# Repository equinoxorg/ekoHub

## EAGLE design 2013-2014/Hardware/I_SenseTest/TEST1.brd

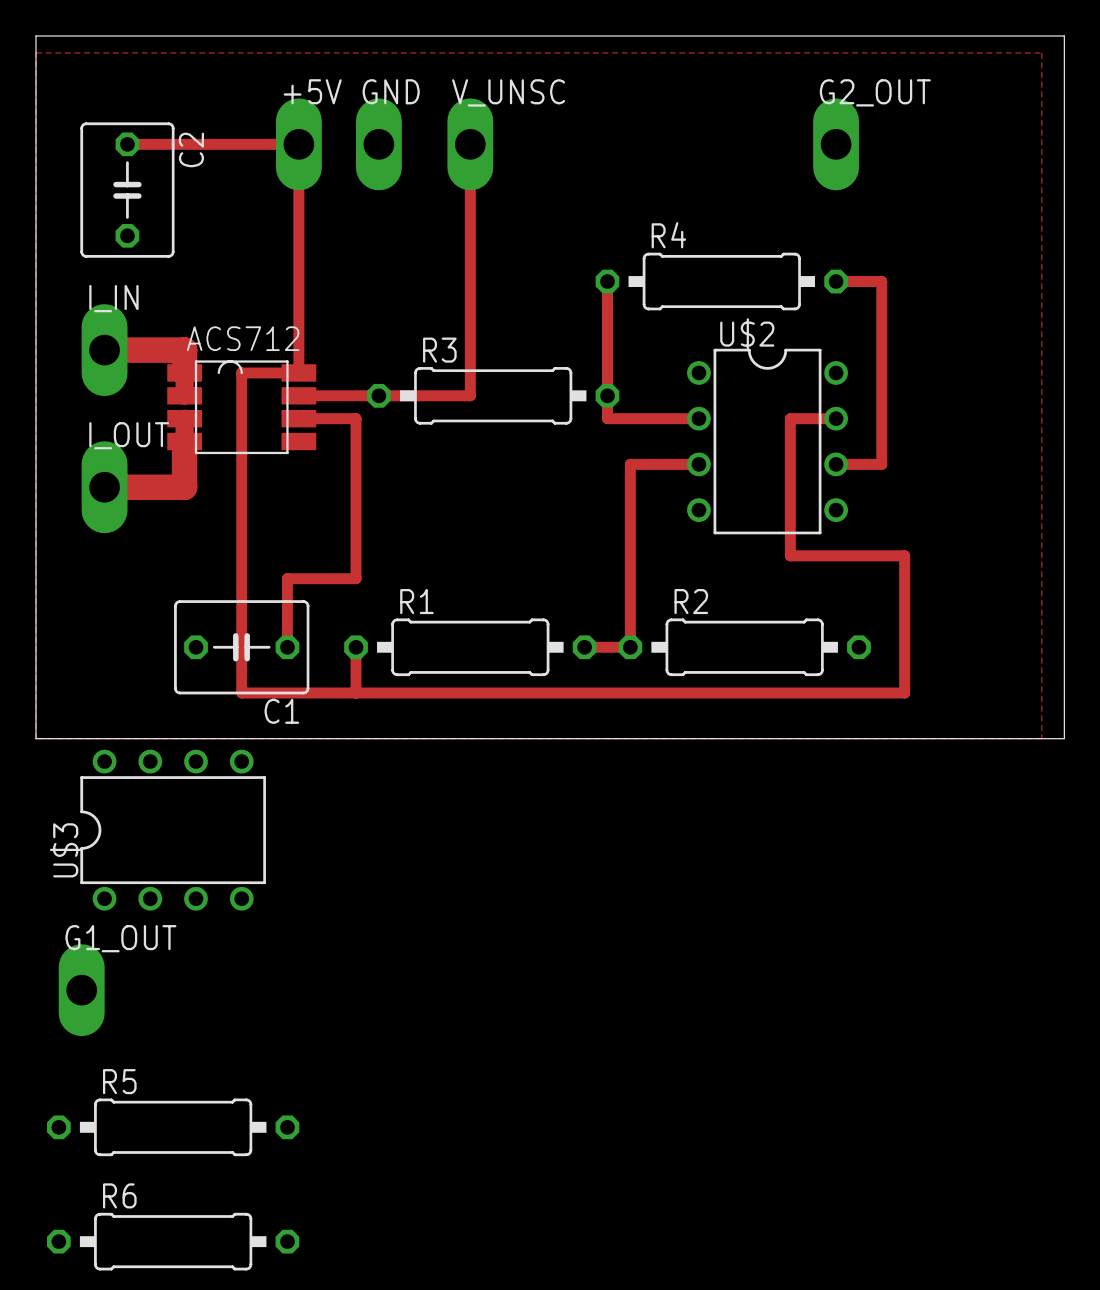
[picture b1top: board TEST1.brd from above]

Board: 2 copper layers, 57.1 x 39.0 mm, 18 parts (0 on the bottom side), 11 nets.

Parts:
+5V: TPPAD1-17Y; P1-17Y
C1: 1n; C050-050X075
C2: 100n; C050-050X075
G1_OUT, G2_OUT: TPPAD1-17Y; P1-17Y
GND: TPPAD1-17Y; P1-17Y
I_IN: TPPAD1-17Y; P1-17Y
I_OUT: TPPAD1-17Y; P1-17Y
R1, R2, R3, R6: 1k; 0309/12
R4: 1.5k; 0309/12
R5: 2k; 0309/12
U$1: ACS712; SOIC8
U$2, U$3: MCP601; PDIP8
V_UNSC: TPPAD1-17Y; P1-17Y

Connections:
+2.5V: R1.2, R2.1, U$2.3, U$3.3
+5V: +5V.TP, C2.1, R1.1, U$1.8, U$2.7, U$3.7
G1_OUT: G1_OUT.TP, R4.2, R5.1, U$2.6
G2_OUT: G2_OUT.TP, R6.2, U$3.6
GND: C1.2, C2.2, GND.TP, R2.2, U$1.5, U$2.4, U$3.4
I_IN: I_IN.TP, U$1.1, U$1.2
I_OUT: I_OUT.TP, U$1.3, U$1.4
unnamed: R3.1, U$1.7, V_UNSC.TP
unnamed: R3.2, R4.1, U$2.2
unnamed: R5.2, R6.1, U$3.2
unnamed: C1.1, U$1.6

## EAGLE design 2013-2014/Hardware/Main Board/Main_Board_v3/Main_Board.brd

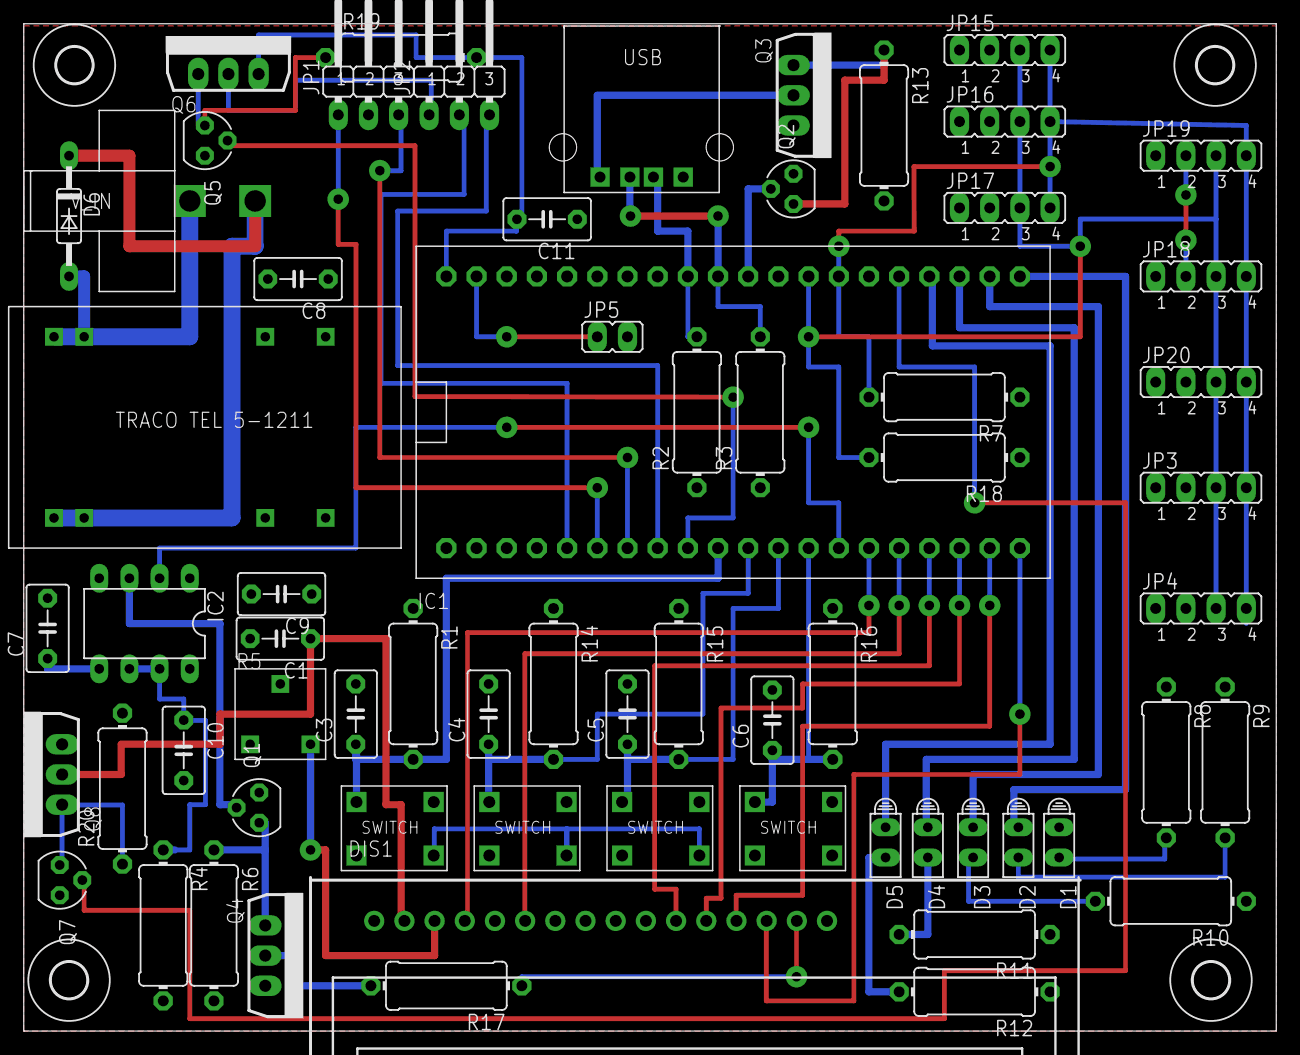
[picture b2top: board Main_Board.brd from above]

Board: 2 copper layers, 105.4 x 84.8 mm, 69 parts (0 on the bottom side), 50 nets.

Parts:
C1, C3, C4, C5, C6, C8, C11: 100nF; C5B3.5
C7: 10nF/0.01u; C5B3.5
C9: 10uF; C5B3.5
C10: 10n; C5B3.5
D1, D2, D3, D4, D5: HLMP6
D6: 1N4148DO35-10; DO35-10
DIS1: TUXGR_16X2_R2
IC1: MBED_MICROCONTROLLER; DIL40_0.9
IC2: NE555; DIL-08
JP1, JP2: JP2W
JP3, JP4, JP15, JP16, JP17, JP18, JP19, JP20: JP4
JP5: JP1
Q1, Q2, Q5, Q7: BS170; SOT54E
Q3, Q4, Q6, Q8: IRF3704L-V; TO262-V
R1, R14, R15, R16: 1K; 0411/12
R2, R3, R7, R8, R9, R10, R11, R12, R18: 0411/12
R4: 300k; 0411/12
R5: IRG2014TRIM
R6, R13, R19, R20: 1M; 0411/12
R17: 20; 0411/12
U$1: USBA_SOCKET
U$4: INPUT_VOLTAGE_CONNECTOR
U$5, U$6, U$7, U$8: TACT_SWITCH
U$9: TRACO_ISOLATED_SUPPLY
U$10, U$11, U$12, U$13: 3,0

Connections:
3V3: JP2.1, Q6.2
3V3_MBED: C11.2, IC1.40, Q6.3, R19.2
5V_MBED: IC1.39, JP5.1
D+: IC1.31, R3.2, U$1.D++
D-: IC1.32, R2.2, U$1.D--
GND: C1.2, C3.2, C4.2, C5.2, C6.2, C7.2, C8.2, C9.2, C10.2, C11.1, DIS1.1, DIS1.5, DIS1.16, IC1.1, IC2.1, JP1.2, JP3.2, JP4.2, JP15.2, JP16.2, JP17.2, JP18.2, JP19.2, JP20.2, Q1.S, Q2.S, Q5.S, Q7.S, R1.1, R2.1, R3.1, R5.P$1, R5.P$2, R8.1, R9.1, R10.1, R11.1, R12.1, R14.1, R15.1, R16.1, U$1.GND, U$9.P$16
MODEM: Q3.2, U$1.5V
unnamed: D1.K, R8.2
unnamed: C7.1, IC2.5
unnamed: DIS1.3, R5.P$3
unnamed: D2.K, R9.2
unnamed: Q2.D, Q3.1, R13.1
unnamed: C10.1, IC2.6, IC2.7, R4.1
unnamed: Q5.D, Q6.1, R19.1
unnamed: Q1.D, Q4.1, R6.1
unnamed: DIS1.15, R17.1
unnamed: Q7.D, Q8.1, R20.1
unnamed: IC2.3, Q1.G
unnamed: Q4.2, R17.2
unnamed: D3.K, R10.2
unnamed: D4.K, R11.2
unnamed: D5.K, R12.2
P5: IC1.5, JP2.2
P6: IC1.6, JP1.1
P7: IC1.7, JP1.3
P8: IC1.8, JP2.3
P9: IC1.9, Q5.G
P10: C3.1, IC1.10, R1.2, U$5.1
P11: C4.1, IC1.11, R14.2, U$6.1
P12: C5.1, IC1.12, R15.2, U$7.1
P13: C6.1, IC1.13, R16.2, U$8.1
P14: IC1.14, IC2.2
P15: DIS1.4, IC1.15
P16: DIS1.6, IC1.16
P17: DIS1.11, IC1.17
P18: DIS1.12, IC1.18
P19: DIS1.13, IC1.19
P20: DIS1.14, IC1.20
P21: D2.A, IC1.21
P22: D3.A, IC1.22
P23: D4.A, IC1.23
P24: D5.A, IC1.24
P25: IC1.25, Q7.G
P30: IC1.30, Q2.G
SCL: IC1.27, JP3.4, JP4.4, JP15.4, JP16.4, JP17.4, JP18.4, JP19.4, JP20.4, R7.2
SDA: IC1.28, JP3.3, JP4.3, JP15.3, JP16.3, JP17.3, JP18.3, JP19.3, JP20.3, R18.2
VIN: C8.1, C9.1, D1.A, IC1.2, IC2.4, IC2.8, JP3.1, JP4.1, JP5.2, JP15.1, JP16.1, JP17.1, JP18.1, JP19.1, JP20.1, Q3.3, Q4.3, Q8.3, R4.2, R6.2, R7.1, R13.2, R18.1, R20.2, U$5.4, U$6.4, U$7.4, U$8.4, U$9.P$14
VIN+: D6.A, U$4.V+, U$9.P$22, U$9.P$23
VIN-: D6.C, U$4.V-, U$9.P$2, U$9.P$3
VIN_LCD: C1.1, DIS1.2, Q8.2

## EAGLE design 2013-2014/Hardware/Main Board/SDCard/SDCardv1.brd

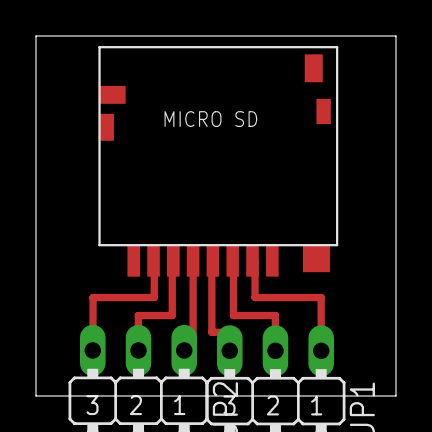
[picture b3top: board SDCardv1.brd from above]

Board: 2 copper layers, 20.0 x 20.0 mm, 3 parts (0 on the bottom side), 6 nets.

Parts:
JP1, JP2: JP2W
U$1: MICROSD_SOCKET

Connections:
unnamed: JP1.1, U$1.CS
unnamed: JP1.2, U$1.DI
unnamed: JP1.3, U$1.VDD
unnamed: JP2.1, U$1.CLK
unnamed: JP2.2, U$1.VSS
unnamed: JP2.3, U$1.DO

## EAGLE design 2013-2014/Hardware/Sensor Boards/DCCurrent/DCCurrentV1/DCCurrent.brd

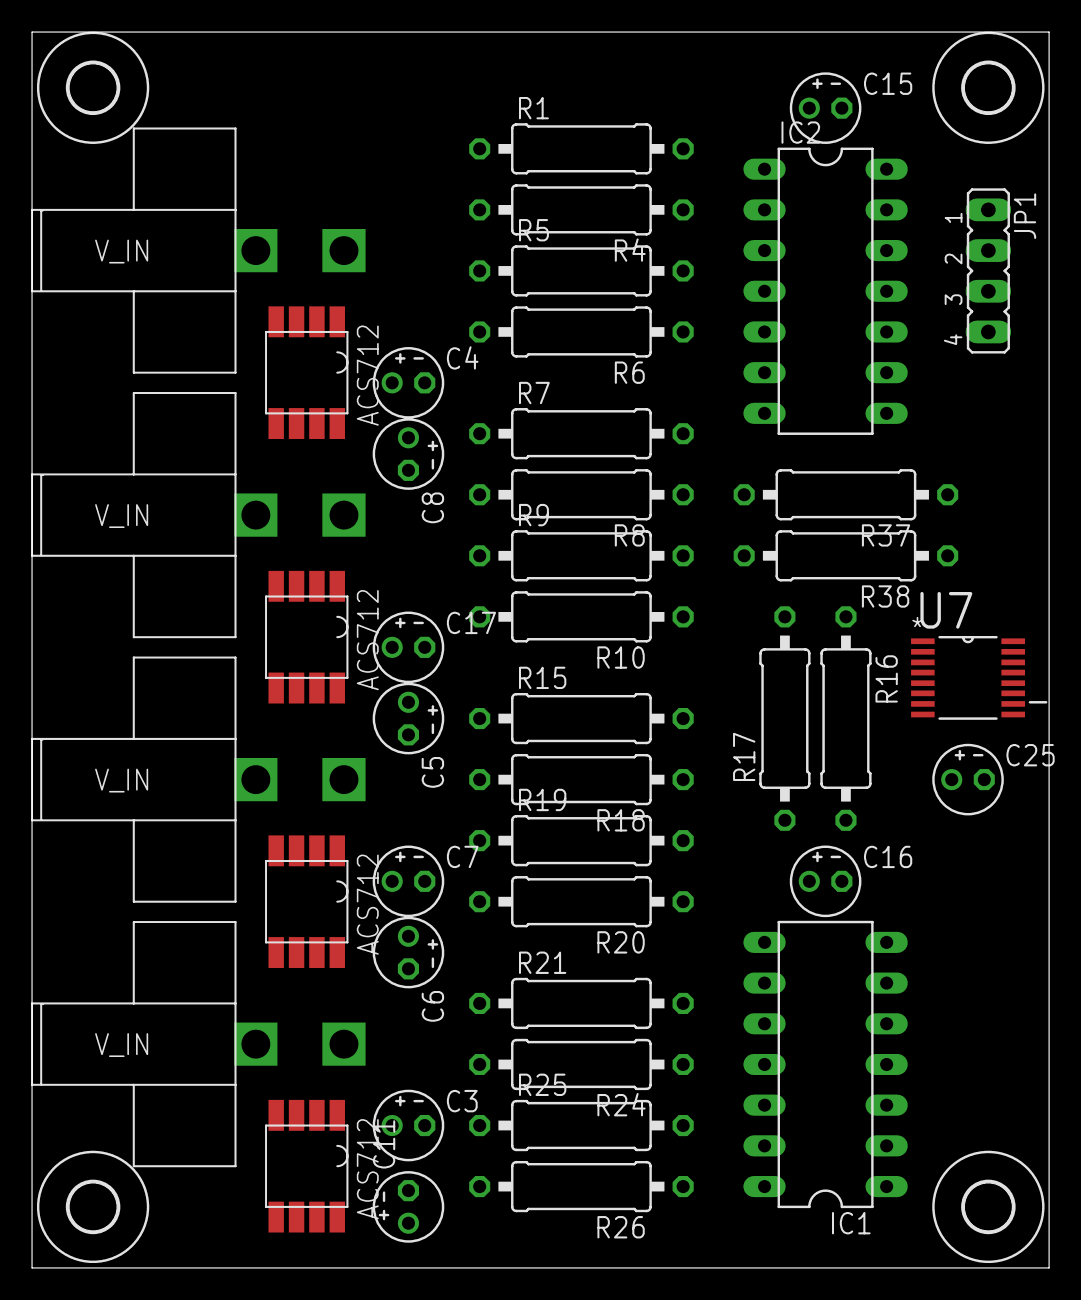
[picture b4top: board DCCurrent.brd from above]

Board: 2 copper layers, 63.5 x 77.1 mm, 47 parts (0 on the bottom side), 37 nets, no tracks yet.

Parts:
C3, C4, C5, C6, C7, C8, C11, C15, C16, C17, C25: E2-4
IC1, IC2: MCP604P; DIL14
JP1: JP4
R1, R6, R7, R10, R15, R16, R17, R20, R21, R26: 1k; 0309/12
R4, R8, R18, R24, R37, R38: 1.5k; 0309/12
R5, R9, R19, R25: 2k; 0309/12
U7: AD7993BRUZ-0; SOP65P640X120-16N
U$1, U$4, U$9, U$11: ACS712; SOIC8
U$2, U$3, U$5, U$6: INPUT_VOLTAGE_CONNECTOR
U$7, U$8, U$10, U$12: 3,0

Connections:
2.5V: IC1.3, IC1.5, IC1.10, IC1.12, IC2.3, IC2.5, IC2.10, IC2.12, R16.1, R17.2
+5V: C3.+, C6.+, C8.+, C15.+, C16.+, C17.+, C25.+, IC1.4, IC2.4, JP1.1, R16.2, R37.1, R38.1, U7.5, U7.6, U7.11, U$1.8, U$4.8, U$9.8, U$11.8
GND: C3.-, C4.-, C5.-, C6.-, C7.-, C8.-, C11.-, C15.-, C16.-, C17.-, C25.-, IC1.11, IC2.11, JP1.2, R17.1, U7.1, U7.2, U7.3, U7.4, U7.16, U$1.5, U$4.5, U$9.5, U$11.5
unnamed: U$1.3, U$1.4, U$6.V+
unnamed: U$1.1, U$1.2, U$6.V-
unnamed: R1.1, U$1.7
unnamed: IC2.2, R1.2, R4.1
unnamed: C4.+, U$1.6
unnamed: IC2.1, R4.2, R5.1
unnamed: IC2.6, R5.2, R6.1
unnamed: U$4.3, U$4.4, U$5.V+
unnamed: U$4.1, U$4.2, U$5.V-
unnamed: R7.1, U$4.7
unnamed: IC2.9, R7.2, R8.1
unnamed: C5.+, U$4.6
unnamed: IC2.8, R8.2, R9.1
unnamed: U$3.V+, U$9.3, U$9.4
unnamed: IC2.13, R9.2, R10.1
unnamed: U$3.V-, U$9.1, U$9.2
unnamed: R15.1, U$9.7
unnamed: IC1.2, R15.2, R18.1
unnamed: C7.+, U$9.6
unnamed: IC1.6, R19.2, R20.1
unnamed: IC1.1, R18.2, R19.1
unnamed: U$2.V+, U$11.3, U$11.4
unnamed: U$2.V-, U$11.1, U$11.2
unnamed: R21.1, U$11.7
unnamed: IC1.9, R21.2, R24.1
unnamed: C11.+, U$11.6
unnamed: IC1.8, R24.2, R25.1
unnamed: IC1.13, R25.2, R26.1
SCL: JP1.4, R37.2, U7.15
SDA: JP1.3, R38.2, U7.14
VAC_OUT1: IC1.7, R20.2, U7.7
VAC_OUT2: IC1.14, R26.2, U7.10
VAC_OUT3: IC2.14, R10.2, U7.9
VAC_OUT4: IC2.7, R6.2, U7.8

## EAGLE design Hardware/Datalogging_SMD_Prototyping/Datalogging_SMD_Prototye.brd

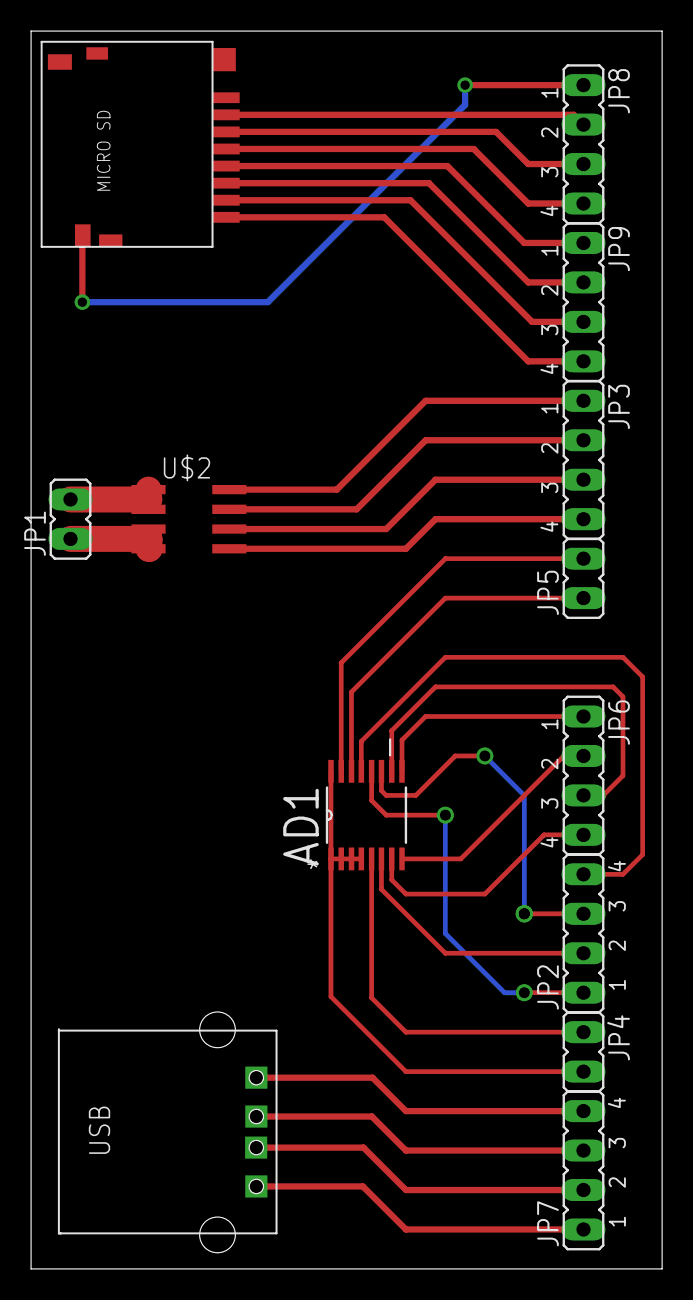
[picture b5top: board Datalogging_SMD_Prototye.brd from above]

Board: 2 copper layers, 40.6 x 79.7 mm, 13 parts (0 on the bottom side), 30 nets.

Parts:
AD1: AD7993BRUZ-0; SOP65P640X120-16N
JP1, JP4, JP5: JP1
JP2, JP3, JP6, JP7, JP8, JP9: JP4
U$1: USBA_SOCKET
U$2: ACS712; SO8
U$3: MICROSD_SOCKET

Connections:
unnamed: JP1.1, U$2.3, U$2.4
unnamed: JP1.2, U$2.1, U$2.2
unnamed: AD1.5, JP4.1
unnamed: AD1.11, JP2.3
unnamed: AD1.1, AD1.2, AD1.3, AD1.4, AD1.16, JP4.2
unnamed: JP3.2, U$2.7
unnamed: JP3.3, U$2.6
unnamed: AD1.6, JP2.2
unnamed: AD1.12, JP2.1
unnamed: AD1.13, JP2.4
unnamed: AD1.7, JP6.4
unnamed: AD1.10, JP6.3
unnamed: AD1.8, JP6.2
unnamed: AD1.9, JP6.1
unnamed: JP7.4, U$1.GND
unnamed: JP7.3, U$1.D-
unnamed: JP7.2, U$1.D+
unnamed: JP7.1, U$1.5V
unnamed: JP8.1, U$3.CD
unnamed: JP8.2, U$3.CS
unnamed: JP8.3, U$3.DI
unnamed: JP8.4, U$3.VDD
unnamed: JP9.1, U$3.CLK
unnamed: JP9.2, U$3.VSS
unnamed: JP9.3, U$3.DO
unnamed: JP9.4, U$3.RSV
unnamed: JP3.4, U$2.5
unnamed: JP3.1, U$2.8
SCL: AD1.15, JP5.2
SDA: AD1.14, JP5.1

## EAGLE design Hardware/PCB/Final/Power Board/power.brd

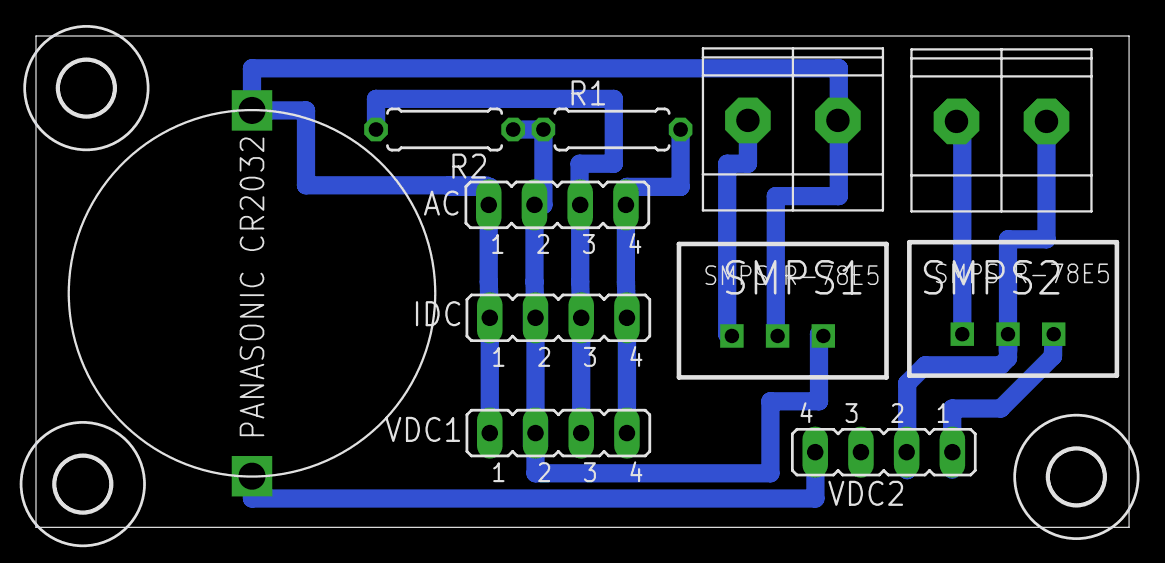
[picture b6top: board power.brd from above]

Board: 2 copper layers, 60.7 x 27.3 mm, 14 parts (0 on the bottom side), 9 nets.

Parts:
AC: JP4
IDC: JP4
R1, R2: 0207/7
U$1, U$2: CTB1500/2; CTB1500-2
U$3: PANASONIC_CR2032
U$4, U$5: SMPS_R-78E5
U$6, U$7, U$8: 3,0
VDC1, VDC2: JP4

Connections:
+5V/1: AC.2, IDC.2, R1.1, R2.1, U$5.VOUT, VDC1.2
+5V/2: U$4.VOUT, VDC2.1
+12V/1: U$2.P$1, U$5.VIN
+12V/2: U$1.P$1, U$4.VIN
GND1: AC.1, IDC.1, U$2.P$2, U$3.GND, U$5.GND, VDC1.1
GND2: U$1.P$2, U$4.GND, VDC2.2
SCL: AC.4, IDC.4, R1.2, VDC1.4
SDA: AC.3, IDC.3, R2.2, VDC1.3
VB: U$3.VB, VDC2.4

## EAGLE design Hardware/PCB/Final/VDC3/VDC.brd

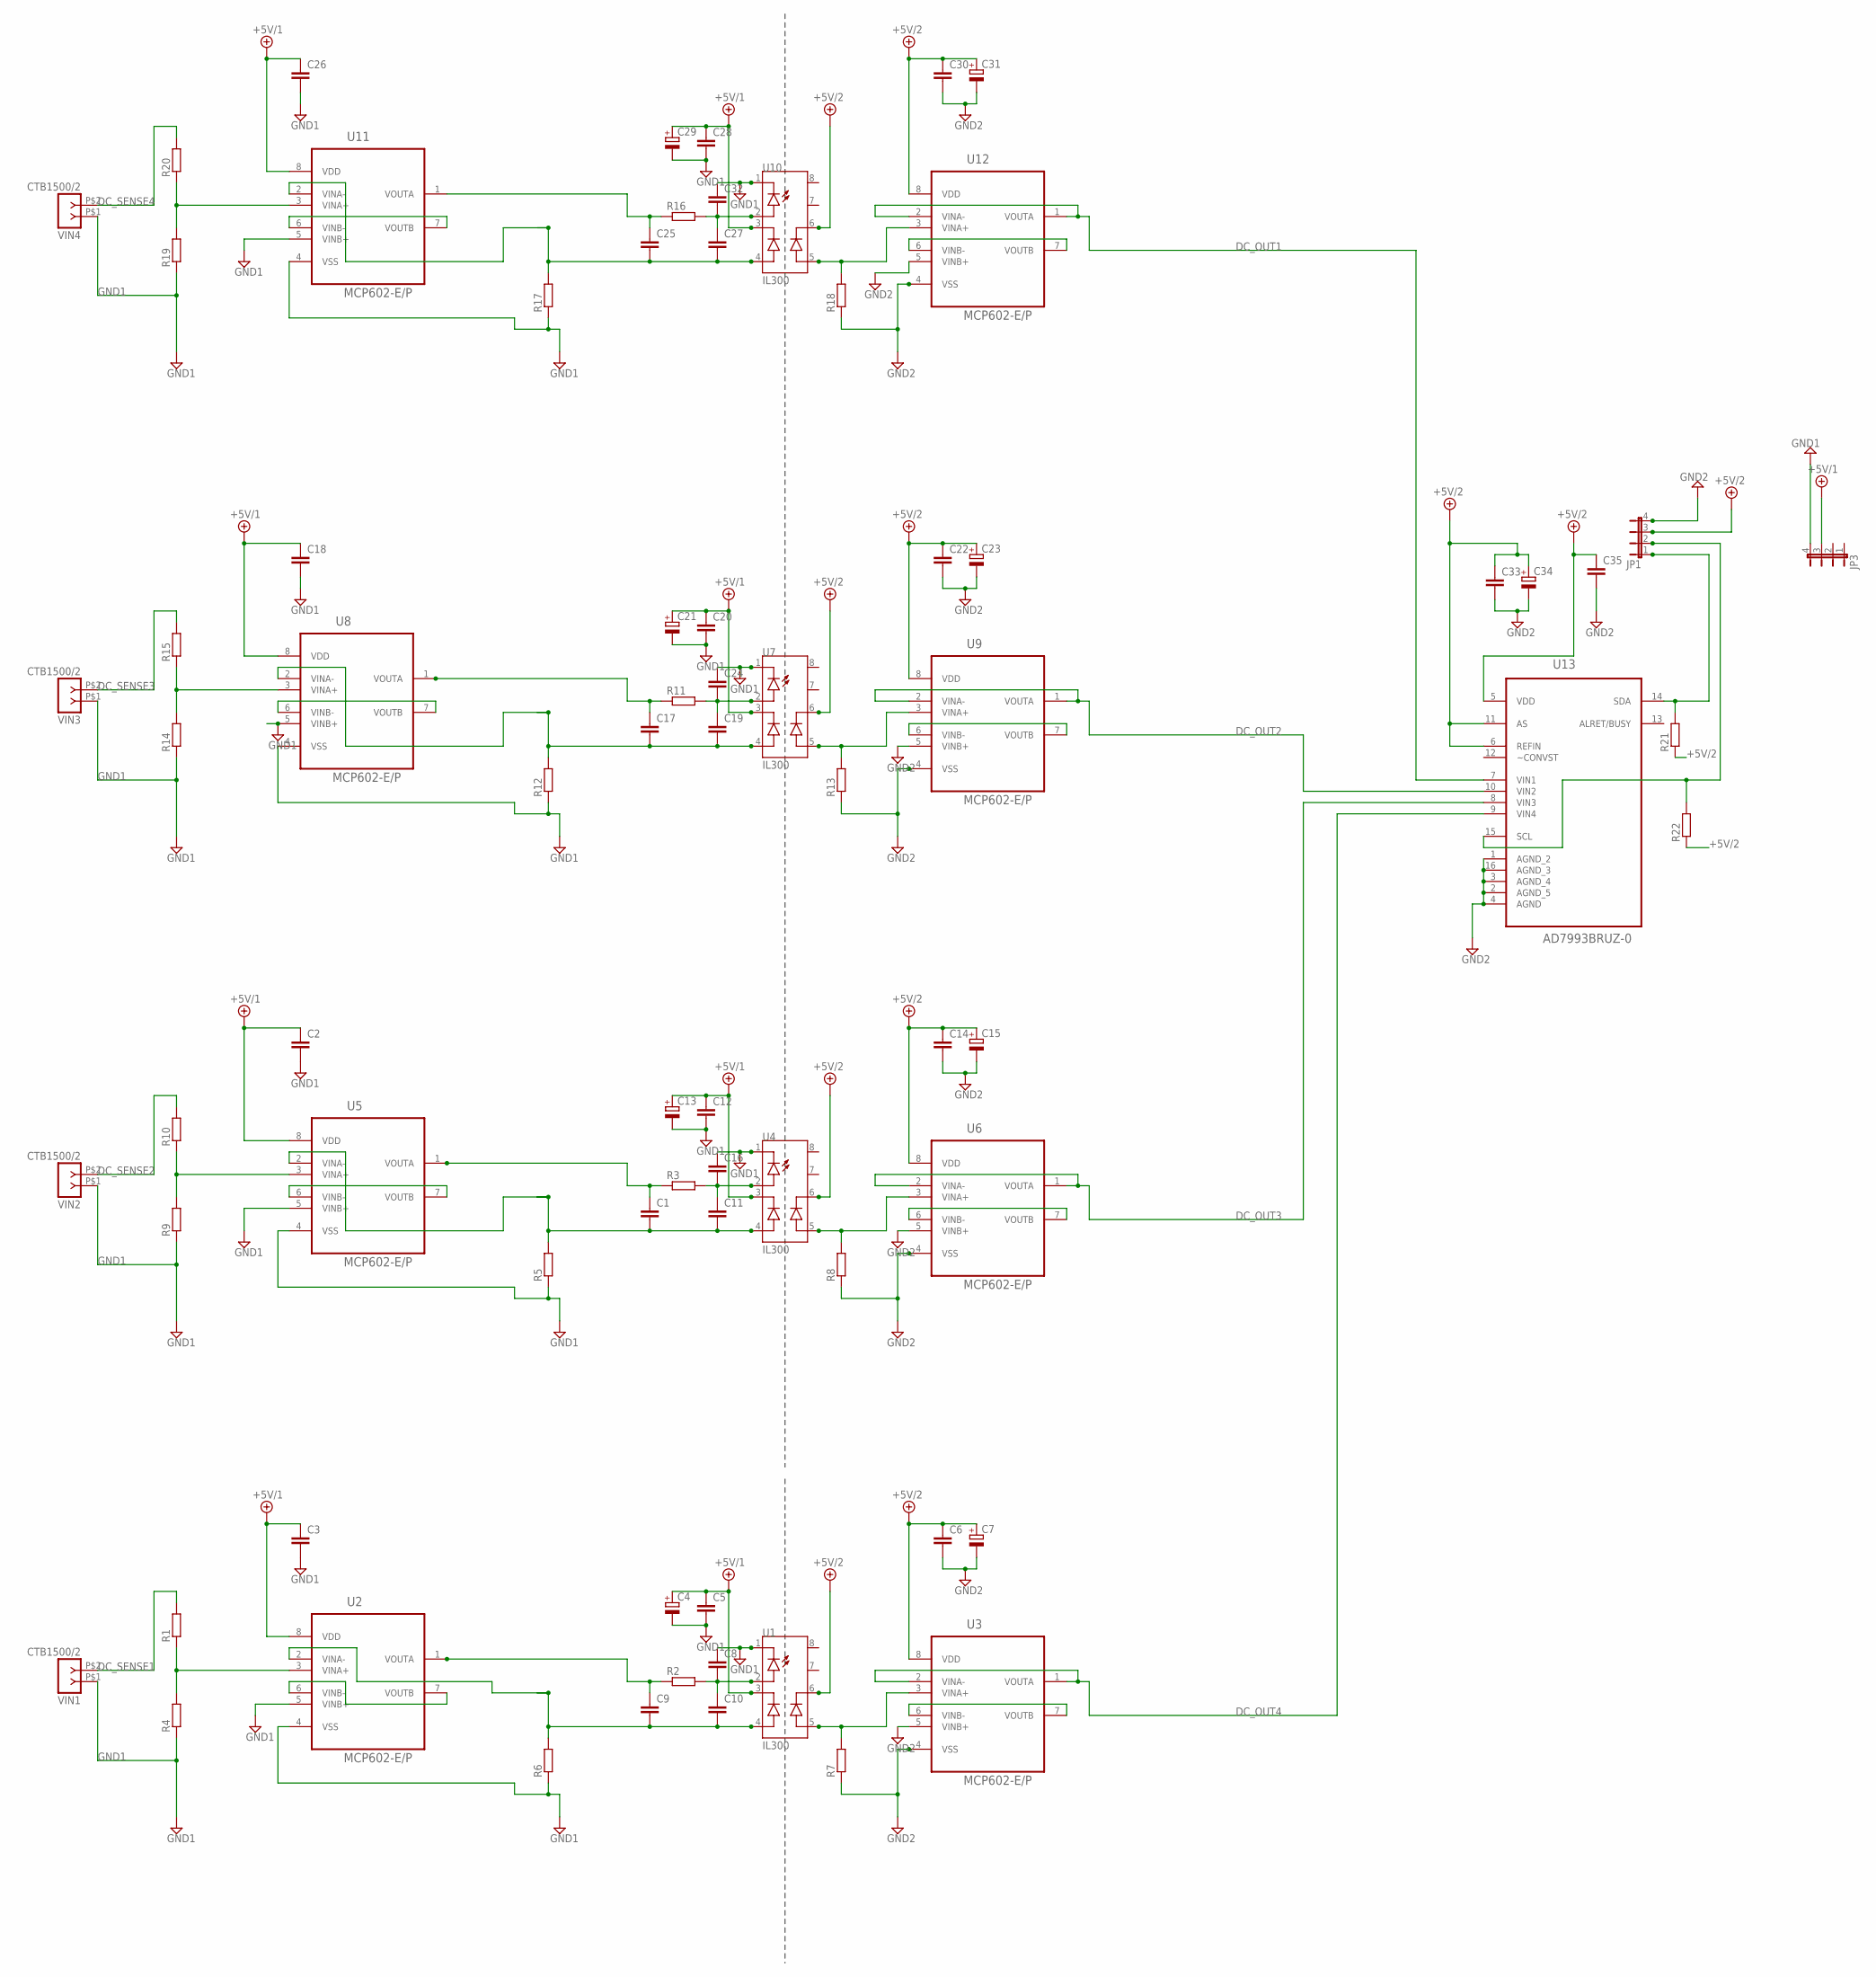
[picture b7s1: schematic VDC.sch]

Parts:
C1, C2, C3, C5, C6, C8, C9, C10, C11, C12, C14, C16, C17, C18, C19, C20, C22, C24, C25, C26, C27, C28, C30, C32: C-EU025-040X050; C025-040X050
C4, C7, C13, C15, C21, C23, C29, C31: CPOL-EUE2-5; E2-5
C33: C-EU025-024X044; C025-024X044
C34: CPOL-EUE2-4; E2-4
C35: C-EU025-025X050; C025-025X050
JP1, JP3: JP4E; JP4
R1, R2, R3, R4, R5, R6, R7, R8, R9, R10, R11, R12, R13, R14, R15, R16, R17, R18, R19, R20, R21, R22: R-EU_0207/10; 0207/10
U1, U4, U7, U10: IL300; DIL08
U2, U3, U5, U6, U8, U9, U11, U12: MCP602-E/P; DIP254P762X508-8P
U13: AD7993BRUZ-0; SOP65P640X120-16N
VIN1, VIN2, VIN3, VIN4: CTB1500/2; CTB1500-2

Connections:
+5V/1: C2.1, C3.1, C4.+, C5.1, C12.1, C13.+, C18.1, C20.1, C21.+, C26.1, C28.1, C29.+, JP3.3, U1.3 (C_FB), U2.8 (VDD), U4.3 (C_FB), U5.8 (VDD), U7.3 (C_FB), U8.8 (VDD), U10.3 (C_FB), U11.8 (VDD)
+5V/2: C6.1, C7.+, C14.1, C15.+, C22.1, C23.+, C30.1, C31.+, C33.1, C34.+, C35.1, JP1.3, R21.1, R22.1, U1.6 (C_OUT), U3.8 (VDD), U4.6 (C_OUT), U6.8 (VDD), U7.6 (C_OUT), U9.8 (VDD), U10.6 (C_OUT), U12.8 (VDD), U13.5 (VDD), U13.6 (REFIN), U13.11 (AS)
DC_OUT1: U12.1 (VOUTA), U12.2 (VINA-), U13.7 (VIN1)
DC_OUT2: U9.1 (VOUTA), U9.2 (VINA-), U13.10 (VIN2)
DC_OUT3: U6.1 (VOUTA), U6.2 (VINA-), U13.8 (VIN3)
DC_OUT4: U3.1 (VOUTA), U3.2 (VINA-), U13.9 (VIN4)
DC_SENSE1: R1.2, VIN1.P$2 (2)
DC_SENSE2: R10.2, VIN2.P$2 (2)
DC_SENSE3: R15.2, VIN3.P$2 (2)
DC_SENSE4: R20.2, VIN4.P$2 (2)
GND2: C6.2, C7.-, C14.2, C15.-, C22.2, C23.-, C30.2, C31.-, C33.2, C34.-, C35.2, JP1.4, R7.1, R8.1, R13.1, R18.1, U3.4 (VSS), U3.5 (VINB+), U6.4 (VSS), U6.5 (VINB+), U9.4 (VSS), U9.5 (VINB+), U12.4 (VSS), U12.5 (VINB+), U13.1 (AGND_2), U13.2 (AGND_5), U13.3 (AGND_4), U13.4 (AGND), U13.16 (AGND_3)
unnamed: C9.2, C10.2, R6.2, U1.4 (A_FB), U2.2 (VINA-)
unnamed: C1.2, C11.2, R5.2, U4.4 (A_FB), U5.2 (VINA-)
unnamed: R7.2, U1.5 (A_OUT), U3.3 (VINA+)
unnamed: C8.2, C10.1, R2.2, U1.2 (A_LED)
unnamed: C9.1, R2.1, U2.1 (VOUTA)
unnamed: C11.1, C16.2, R3.2, U4.2 (A_LED)
unnamed: C1.1, R3.1, U5.1 (VOUTA)
unnamed: R1.1, R4.2, U2.3 (VINA+)
unnamed: R8.2, U4.5 (A_OUT), U6.3 (VINA+)
unnamed: R9.2, R10.1, U5.3 (VINA+)
unnamed: C17.2, C19.2, R12.2, U7.4 (A_FB), U8.2 (VINA-)
unnamed: C19.1, C24.2, R11.2, U7.2 (A_LED)
unnamed: C17.1, R11.1, U8.1 (VOUTA)
unnamed: R13.2, U7.5 (A_OUT), U9.3 (VINA+)
unnamed: R14.2, R15.1, U8.3 (VINA+)
unnamed: C25.2, C27.2, R17.2, U10.4 (A_FB), U11.2 (VINA-)
unnamed: C27.1, C32.2, R16.2, U10.2 (A_LED)
unnamed: C25.1, R16.1, U11.1 (VOUTA)
unnamed: R18.2, U10.5 (A_OUT), U12.3 (VINA+)
unnamed: R19.2, R20.1, U11.3 (VINA+)
unnamed: JP1.1, R21.2, U13.14 (SDA)
unnamed: JP1.2, R22.2, U13.15 (SCL)
unnamed: U11.6 (VINB-), U11.7 (VOUTB)
unnamed: U12.6 (VINB-), U12.7 (VOUTB)
unnamed: U8.6 (VINB-), U8.7 (VOUTB)
unnamed: U9.6 (VINB-), U9.7 (VOUTB)
unnamed: U5.6 (VINB-), U5.7 (VOUTB)
unnamed: U6.6 (VINB-), U6.7 (VOUTB)
unnamed: U2.6 (VINB-), U2.7 (VOUTB)
unnamed: U3.6 (VINB-), U3.7 (VOUTB)

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
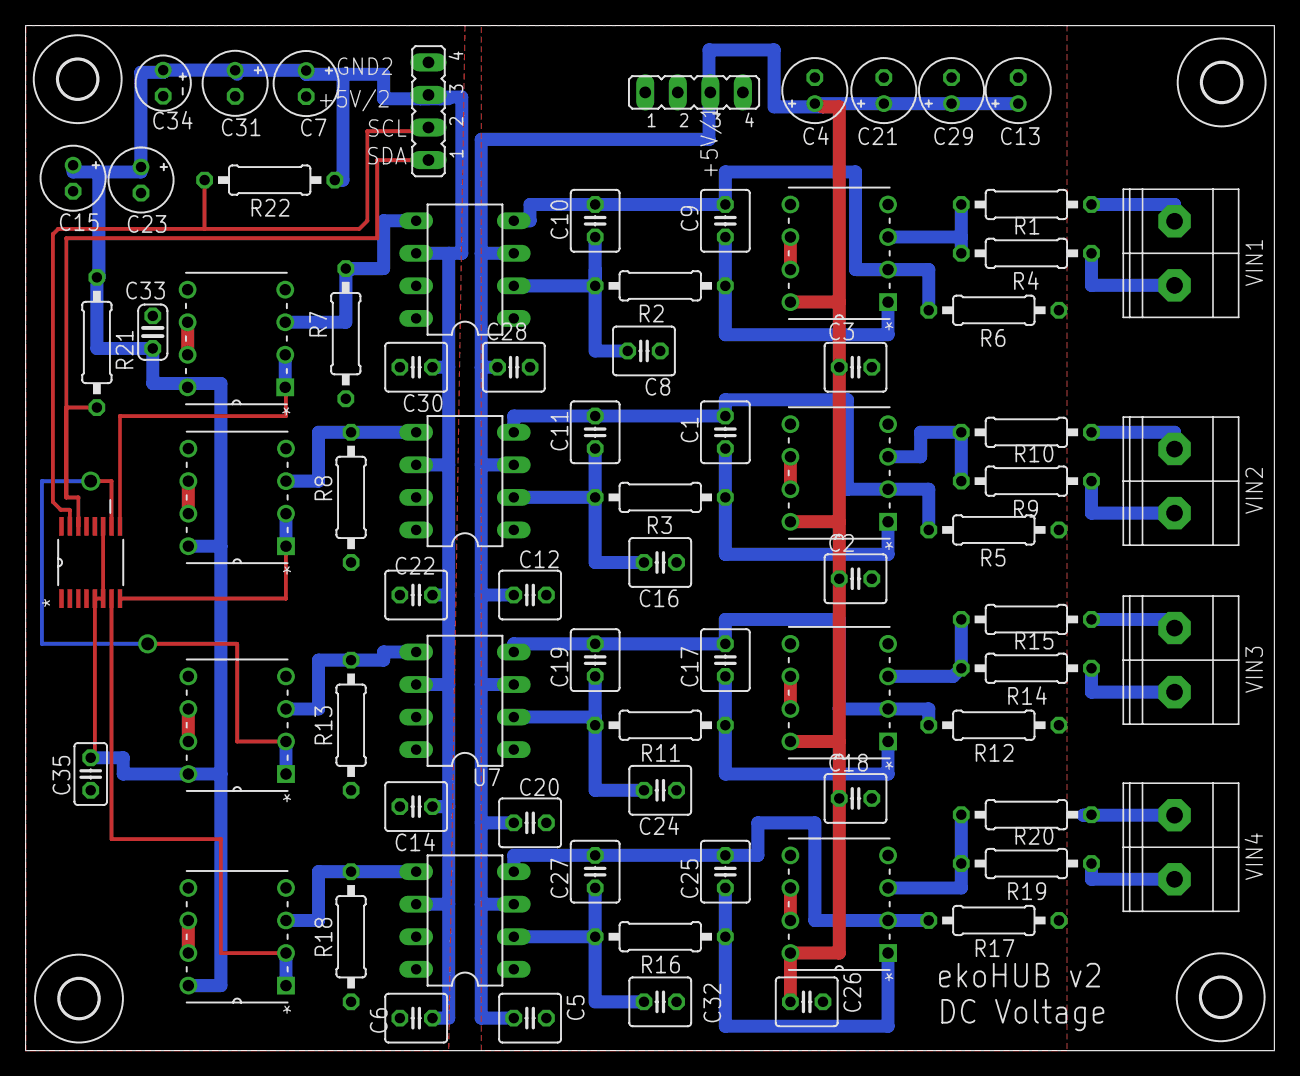
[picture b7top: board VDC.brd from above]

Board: 2 copper layers, 97.5 x 80.0 mm, 80 parts (0 on the bottom side), 46 nets.

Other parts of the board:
U$1, U$2, U$3, U$4: 3,0
